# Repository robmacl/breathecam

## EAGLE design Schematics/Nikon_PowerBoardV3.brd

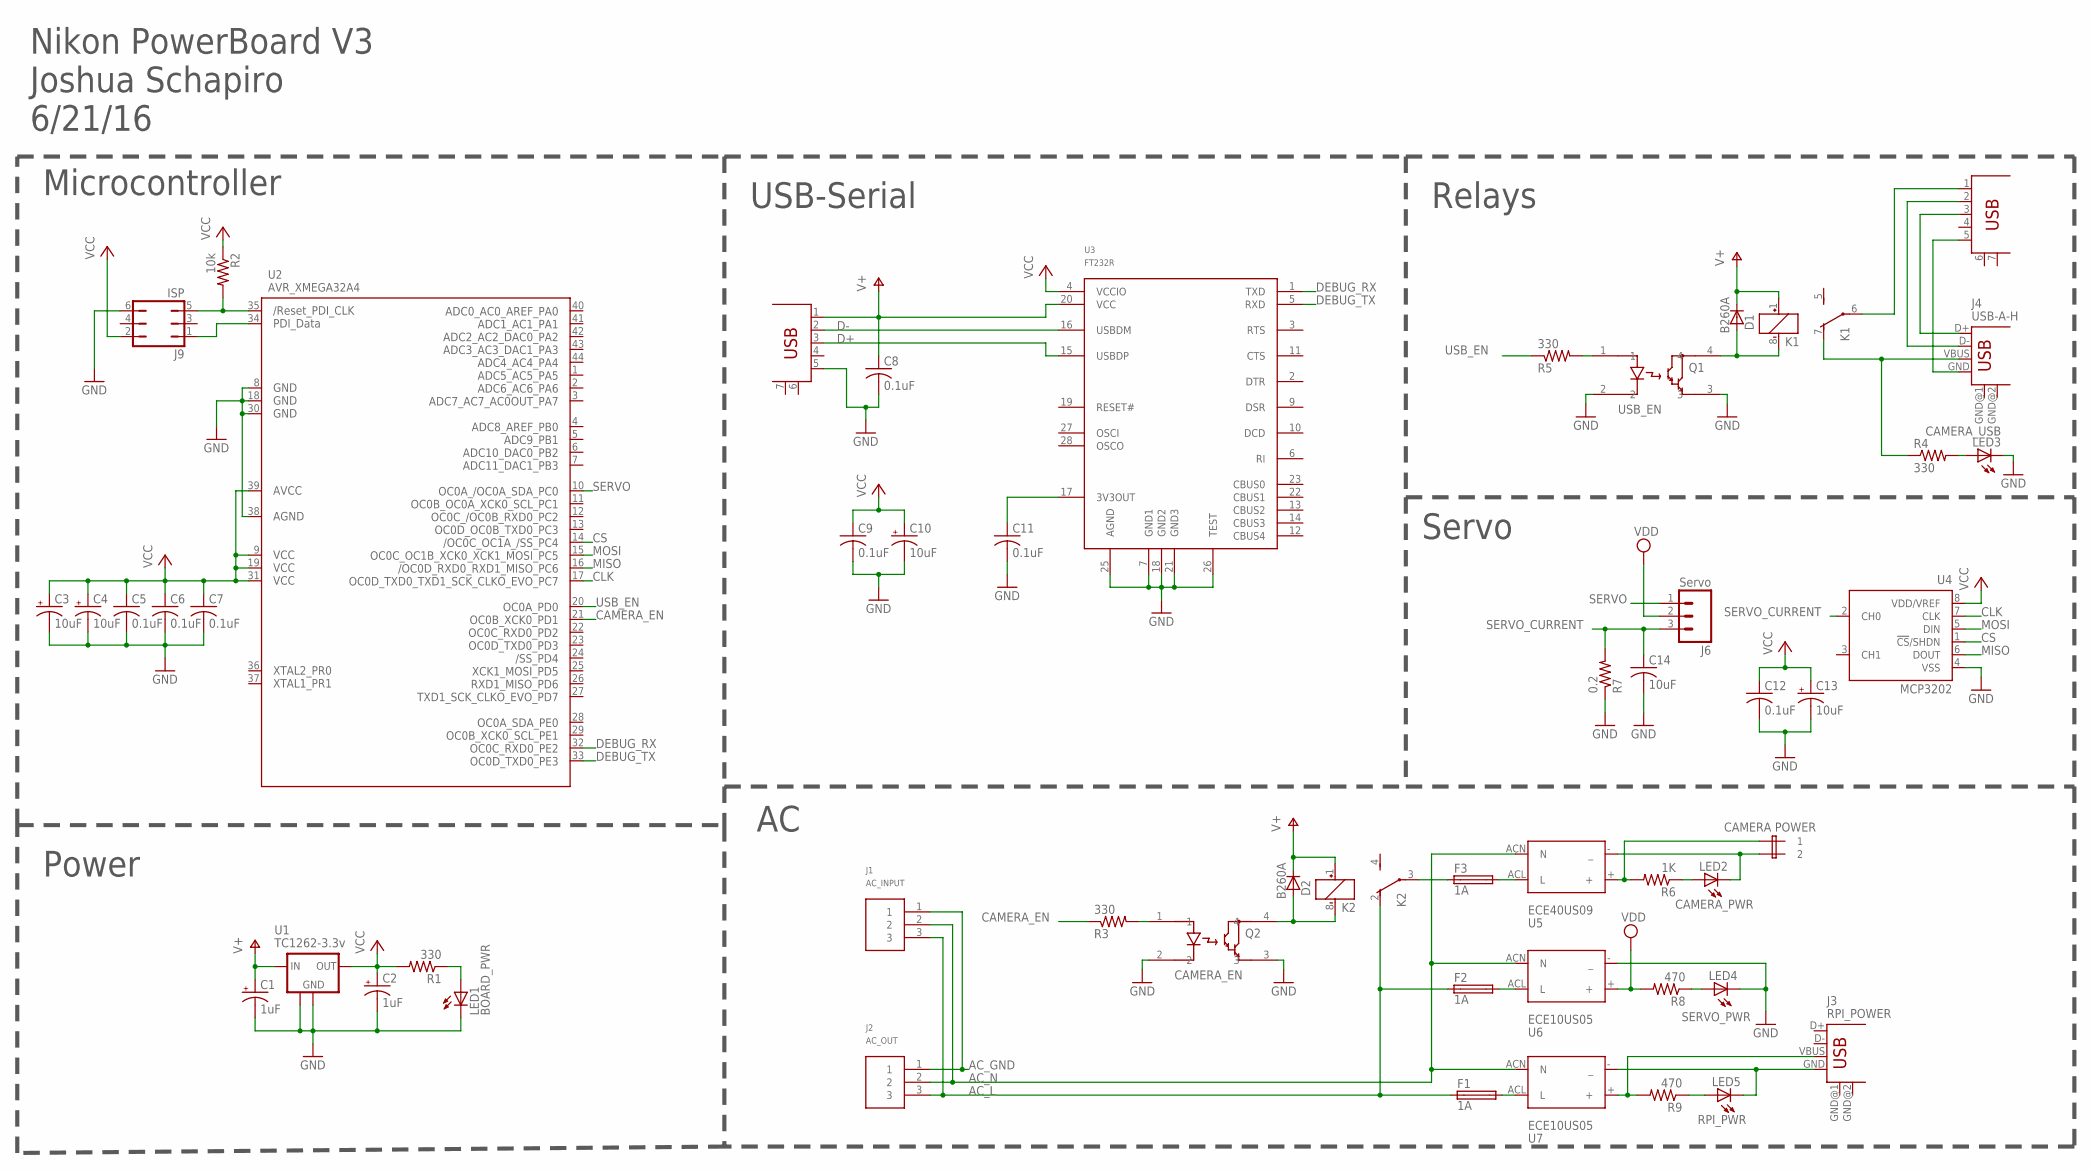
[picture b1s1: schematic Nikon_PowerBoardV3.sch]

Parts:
C1, C2: 1uF; EIA3216
C3, C4, C10, C13: 10uF; EIA3216
C5, C6, C7, C8, C9, C11, C12: 0.1uF; C0603
C14: 10uF; C1206
D1, D2: B260A; SMA-DIODE
F1, F2, F3: 1A; 19560
J1: AC_INPUT; 3-PIN-SCREW
J2: AC_OUT; 3-PIN-SCREW
J3: RPI_POWER; USB-A-H
J4: USB-A-H
J5: CAMERA POWER; 2-PIN_SCREWTERM
J6: Servo; 1X03_LONGPADS
J7, J8: MICRO-USB; MICRO_USB_SM_W/_TO_PINS
J9: ISP; JP3Q
K1: USB_EN; G6K-2F
K2: CAMERA_EN; G6K-2F
LED1: BOARD_PWR; CHIPLED_0603
LED2: CAMERA_PWR; CHIPLED_0603
LED3: CAMERA_USB; CHIPLED_0603
LED4: SERVO_PWR; CHIPLED_0603
LED5: RPI_PWR; CHIPLED_0603
Q1: USB_EN; 4-PIN_MINI-FLAT
Q2: CAMERA_EN; 4-PIN_MINI-FLAT
R1, R3, R4, R5: 330; R0603
R2: 10k; R0603
R6: 1K; R0603
R7: 0.2; R1206
R8, R9: 470; R0603
U1: TC1262-3.3v; SOT223
U2: AVR_XMEGA32A4; TQFP44
U3: FT232R; SSOP28
U4: MCP3202; SO-08
U5: ECE40US09; EC40
U6, U7: ECE10US05; ECE10

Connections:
AC_GND: J1.1, J2.1
AC_L: F1.1, F2.1, J1.3, J2.3, K2.2 (O)
AC_N: J1.2, J2.2, U5.ACN (N), U6.ACN (N), U7.ACN (N)
CAMERA_EN: R3.1, U2.21 (PD1)
CLK: U2.17 (PC7), U4.7 (CLK)
CS: U2.14 (PC4), U4.1 (!CS!/SHDN)
D+: J8.3 (D+), U3.15 (USBDP)
D-: J8.2 (D-), U3.16 (USBDM)
DEBUG_RX: U2.32 (PE2), U3.1 (TXD)
DEBUG_TX: U2.33 (PE3), U3.5 (RXD)
GND: C1.C (-), C2.C (-), C3.C (-), C4.C (-), C5.2, C6.2, C7.2, C8.2, C9.2, C10.C (-), C11.2, C12.2, C13.C (-), C14.2, J8.5 (GND), J9.6, LED1.C, LED3.C, LED4.C, Q1.2, Q1.3, Q2.2, Q2.3, R7.1, U1.2 (GND), U1.4 (GND1), U2.8 (GND1), U2.18 (GND2), U2.30 (GND3), U2.38 (AGND), U3.7 (GND1), U3.18 (GND2), U3.21 (GND3), U3.25 (AGND), U3.26 (TEST), U4.4 (VSS), U6.- (_)
MISO: U2.16 (PC6), U4.6 (DOUT)
MOSI: U2.15 (PC5), U4.5 (DIN)
unnamed: J9.1, U2.34 (PDI_DATA)
unnamed: J4.GND, J7.5 (GND)
unnamed: F3.1, K2.3
unnamed: LED1.A, R1.1
unnamed: Q1.1, R5.2
unnamed: J9.5, R2.2, U2.35 (RESET)
unnamed: D2.A, K2.8 (-), Q2.4
unnamed: J7.1 (VBUS), K1.6
unnamed: LED3.A, R4.2
unnamed: Q2.1, R3.2
unnamed: J3.VBUS, R9.2, U7.+
unnamed: F3.2, U5.ACL (L)
unnamed: F2.2, U6.ACL (L)
unnamed: F1.2, U7.ACL (L)
unnamed: LED4.A, R8.1
unnamed: J5.P$1 (1), R6.2, U5.+
unnamed: C11.1, U3.17 (3V3OUT)
unnamed: LED2.A, R6.1
unnamed: J5.P$2 (2), LED2.C, U5.- (_)
unnamed: J3.GND, LED5.C, U7.- (_)
unnamed: LED5.A, R9.1
unnamed: J4.VBUS, K1.7 (O), R4.1
unnamed: J4.D+, J7.3 (D+)
unnamed: J4.D-, J7.2 (D-)
unnamed: D1.A, K1.8 (-), Q1.4
SERVO: J6.1, U2.10 (PC0)
SERVO_CURRENT: C14.1, J6.3, R7.2, U4.2 (CH0)
USB_EN: R5.1, U2.20 (PD0)
V+: C1.A (+), C8.1, D1.C, D2.C, J8.1 (VBUS), K1.1 (+), K2.1 (+), U1.1 (IN), U3.20 (VCC)
VCC: C2.A (+), C3.A (+), C4.A (+), C5.1, C6.1, C7.1, C9.1, C10.A (+), C12.1, C13.A (+), J9.2, R1.2, R2.1, U1.3 (OUT), U2.9 (VCC1), U2.19 (VCC2), U2.31 (VCC3), U2.39 (AVCC), U3.4 (VCCIO), U4.8 (VDD/VREF)
VDD: J6.2, R8.2, U6.+

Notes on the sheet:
Nikon PowerBoard V3 Joshua Schapiro 6/21/16
Microcontroller
USB-Serial
Relays
Power
Servo
CAMERA POWER

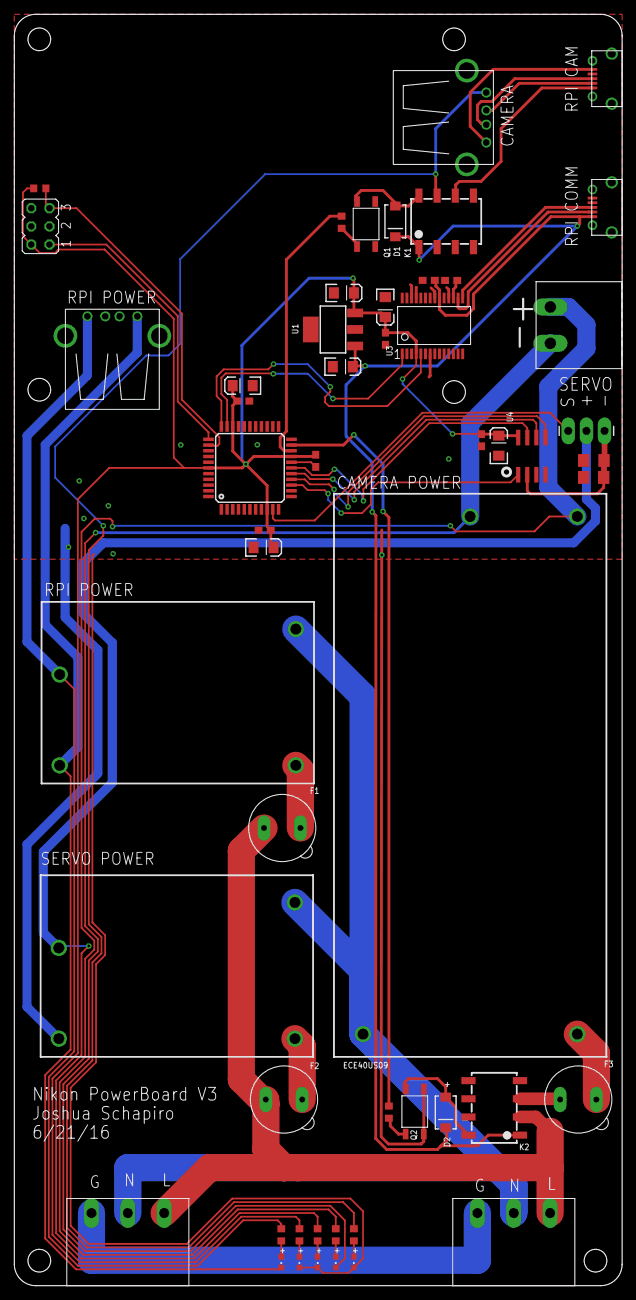
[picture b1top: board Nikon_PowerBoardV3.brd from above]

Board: 2 copper layers, 85.0 x 177.8 mm, 53 parts (0 on the bottom side), 44 nets.

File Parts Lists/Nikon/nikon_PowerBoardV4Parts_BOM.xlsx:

Quantity | Reference | Part | Part Number | Distributor | Manufacturer part number
1 | U2 | Microcontroller | ATXMEGA32A4-AU-ND | Digikey | ATXMEGA32A4-AU
1 | U1 | TC1262-3.0v | TC1262-3.0VDB-ND | Digikey | TC1262-3.0VDB
1 | U3 | FT232R | 768-1007-1-ND | Digikey | FT232RL-REEL
1 | U4 | MCP3202 | MCP3202-CI/SN-ND | Digikey | MCP3202-CI/SN
2 | U6, U7 | 5v supply | 1470-1115-ND | Digikey | ECE10US05
1 | U5 | 9v supply | 1470-1134-ND | Digikey | ECE40US09
2 | Q1, Q2 | 425-2098-1-ND | optocoupler | Digikey | PC365NJ0000F
2 | K1, K2 | Z112CT-ND | relay | Digikey | G6K-2F-TR DC5
5 | LED1, LED2, LED3, LED4, LED5 | 160-1435-1-ND | green leds 0603 | Digikey | LTST-C190KGKT
2 | D1, D2 | B260A-FDICT-ND | diode for relay | Digikey | B260A-13-F
3 | F1, F2, F3 | WK0001-ND | fuse holder | Digikey | 56000001319
2 | J1, J2 | APC1259-ND | 3-pin screw terminal | Digikey | ELFH03210
1 | J5 | 609-3907-ND | screw terminal header | Digikey | 20020110-H021A01LF
2 | J7, J8 | 609-4618-1-ND | usb - micro | Digikey | 10118194-0001LF
2 | J3, J4 | 1175-1015-ND | usb - A | Digikey | 1002-001-01000
1 | J9 | 952-2121-ND | isp header | Digikey | M20-9980346
1 | J6 | 609-3461-ND | 3-pin header | Digikey | 68000-103HLF
4 | R1, R3, R4, R5 | 311-330HRCT-ND | 330R 0603 resistor | Digikey | RC0603FR-07330RL
2 | R8, R9 | 311-470GRCT-ND | 470R 0603 resistor | Digikey | RC0603JR-07470RL
1 | R6 | 311-1.0KGRCT-ND | 1k 0603 resistor | Digikey | RC0603JR-071KL
1 | R2 | P10KGCT-ND | 10k 0603 resistor | Digikey | ERJ-3GEYJ103V
1 | R7 | CRL1206-FW-R200ELFCT-ND | 0.2R 1206 resistor | Digikey | CRL1206-FW-R200ELF
1 | R10 | A121216CT-ND | 300R 2512 resistor | Digikey | 3522300RFT
7 | C5, C6, C7, C8, C9, C11, C12 | 490-1575-1-ND | 0.1uF 0603 ceramic capacitor | Digikey | GRM188F51E104ZA01D
2 | C1, C2 | 399-3678-1-ND | 1uf 1206 tantalum capacitor | Digikey | T491A105K016AT
4 | C3, C4, C10, C13 | 495-2174-1-ND | 10uf 1206 tantalum capacitor | Digikey | T491A106M004AT
1 | C14 | 1276-1312-1-ND | 10uF 1206 cermic capacitor | Digikey | CL31F106ZOHNNNE

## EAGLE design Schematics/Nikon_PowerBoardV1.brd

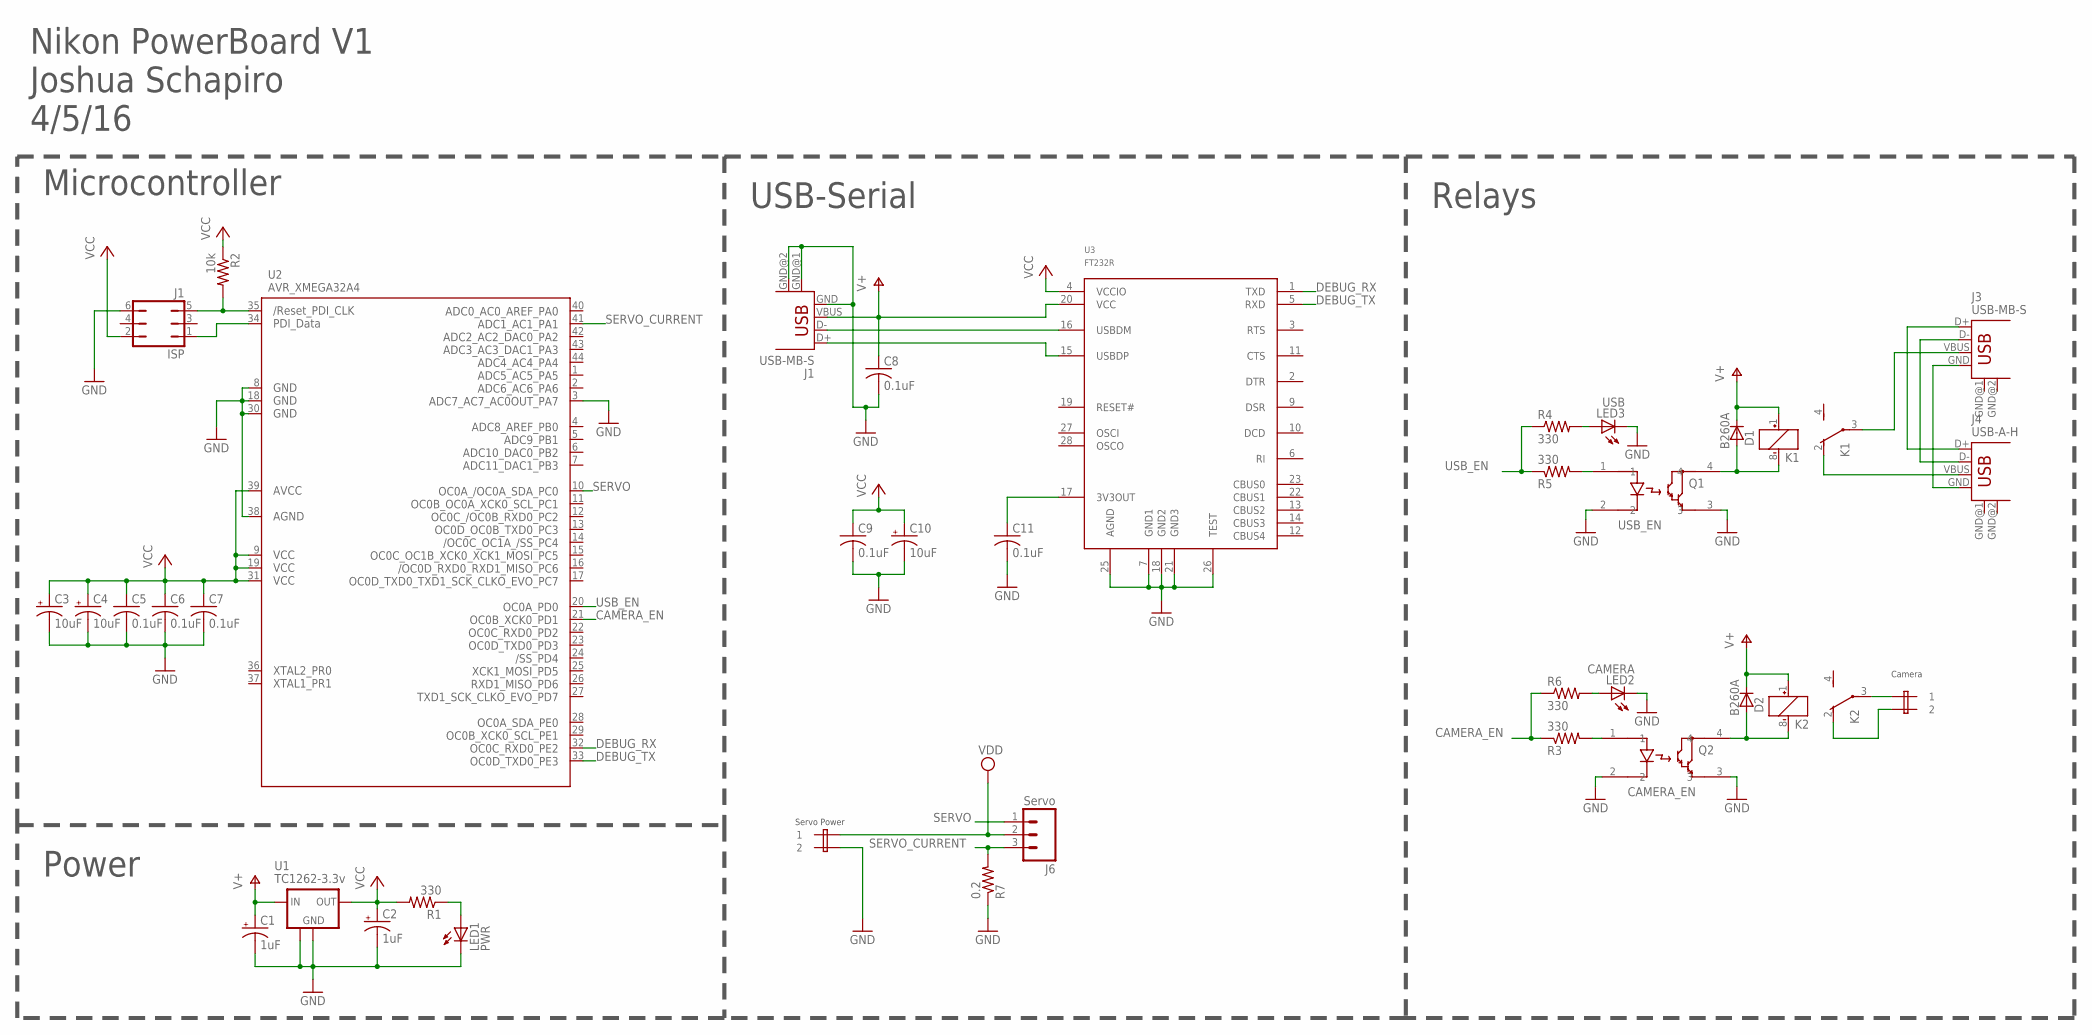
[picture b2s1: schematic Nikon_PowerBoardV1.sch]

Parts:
C1, C2: 1uF; EIA3216
C3, C4, C10: 10uF; EIA3216
C5, C6, C7, C8, C9, C11: 0.1uF; C1206
D1, D2: B260A; SMA-DIODE
ISP: J1; JP3Q
J1, J3: USB-MB-S
J2: Camera; 2-PIN_SCREWTERM
J4: USB-A-H
J5: ServoPower; 2-PIN_SCREWTERM
J6: Servo; 1X03_LONGPADS
K1: USB_EN; G6K-2F
K2: CAMERA_EN; G6K-2F
LED1: PWR; CHIPLED_1206
LED2: CAMERA; CHIPLED_1206
LED3: USB; CHIPLED_1206
Q1: USB_EN; 4-PIN_MINI-FLAT
Q2: CAMERA_EN; 4-PIN_MINI-FLAT
R1, R3, R4, R5, R6: 330; R1206
R2: 10k; R1206
R7: 0.2; R1206
U1: TC1262-3.3v; SOT223
U2: AVR_XMEGA32A4; TQFP44
U3: FT232R; SSOP28

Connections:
CAMERA_EN: R3.1, R6.1, U2.21 (PD1)
DEBUG_RX: U2.32 (PE2), U3.1 (TXD)
DEBUG_TX: U2.33 (PE3), U3.5 (RXD)
GND: C1.C (-), C2.C (-), C3.C (-), C4.C (-), C5.2, C6.2, C7.2, C8.2, C9.2, C10.C (-), C11.2, ISP.6, J1.GND, J1.GND@1 (GND), J1.GND@2 (GND), J5.P$2 (2), LED1.C, LED2.C, LED3.C, Q1.2, Q1.3, Q2.2, Q2.3, R7.1, U1.2 (GND), U1.4 (GND1), U2.3 (PA7), U2.8 (GND1), U2.18 (GND2), U2.30 (GND3), U2.38 (AGND), U3.7 (GND1), U3.18 (GND2), U3.21 (GND3), U3.25 (AGND), U3.26 (TEST)
J2: J3.D+, J4.D+
unnamed: ISP.1, U2.34 (PDI_DATA)
unnamed: J3.GND, J4.GND
unnamed: J3.D-, J4.D-
unnamed: LED1.A, R1.1
unnamed: Q1.1, R5.2
unnamed: ISP.5, R2.2, U2.35 (RESET)
unnamed: D2.A, K2.8 (-), Q2.4
unnamed: J3.VBUS, K1.3
unnamed: J4.VBUS, K1.2 (O)
unnamed: LED3.A, R4.2
unnamed: Q2.1, R3.2
unnamed: J1.D-, U3.16 (USBDM)
unnamed: J1.D+, U3.15 (USBDP)
unnamed: J2.P$1 (1), K2.3
unnamed: J2.P$2 (2), K2.2 (O)
unnamed: C11.1, U3.17 (3V3OUT)
unnamed: LED2.A, R6.2
unnamed: D1.A, K1.8 (-), Q1.4
SERVO: J6.1, U2.10 (PC0)
SERVO_CURRENT: J6.3, R7.2, U2.41 (PA1)
USB_EN: R4.1, R5.1, U2.20 (PD0)
V+: C1.A (+), C8.1, D1.C, D2.C, J1.VBUS, K1.1 (+), K2.1 (+), U1.1 (IN), U3.20 (VCC)
VCC: C2.A (+), C3.A (+), C4.A (+), C5.1, C6.1, C7.1, C9.1, C10.A (+), ISP.2, R1.2, R2.1, U1.3 (OUT), U2.9 (VCC1), U2.19 (VCC2), U2.31 (VCC3), U2.39 (AVCC), U3.4 (VCCIO)
VDD: J5.P$1 (1), J6.2

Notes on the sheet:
Camera
Nikon PowerBoard V1 Joshua Schapiro 4/5/16
Microcontroller
USB-Serial
Relays
Power
Servo Power

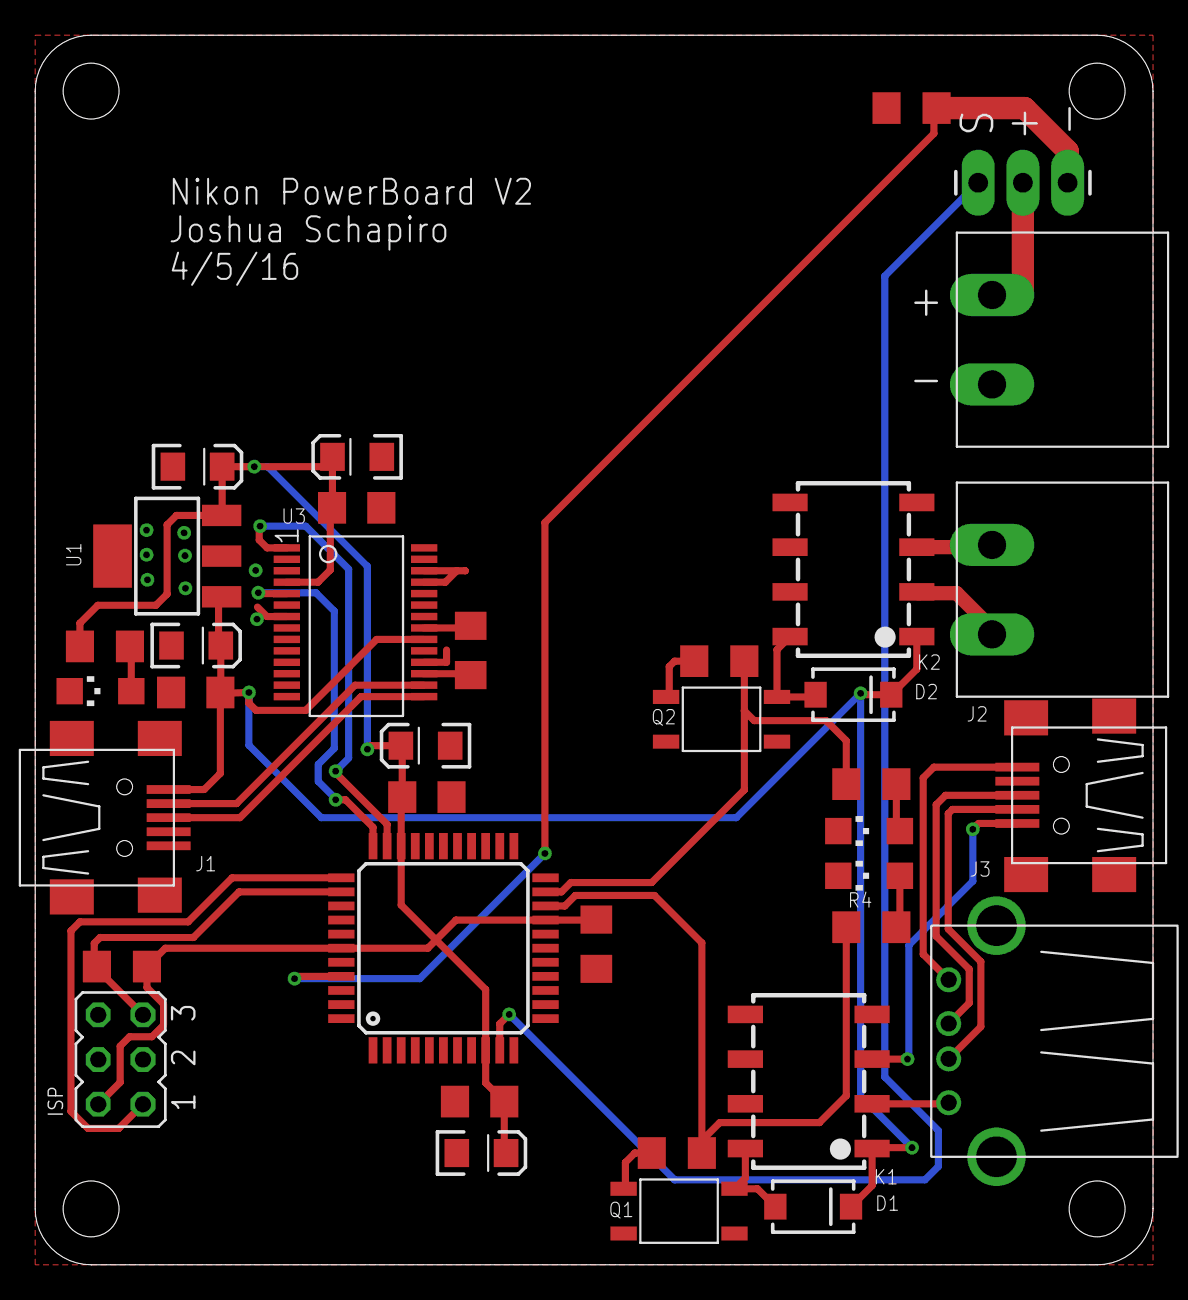
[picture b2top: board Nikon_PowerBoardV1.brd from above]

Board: 2 copper layers, 63.5 x 69.8 mm, 37 parts (0 on the bottom side), 29 nets.

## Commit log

2022-03-16 Code and design files for BreatheCam cameras.
2022-03-23 Deleted old image of the 'requests' package in nikon/install/requests, added new CAD files in CAD/pi_cam
2022-04-05 Modified camera_mount.SLDPRT to allow access to focus lock screw using hex key. Fixed the mounting slots in mount_plate.SLDPRT some more.
2022-04-06 Various changes to improve fit of the mount within the housing. Also added stiffeners to the plate and incorporated the standoffs into the plate.
2022-04-09 Made some test parts for tweaking mounting hole sizes, and moved the mount slots so we are 5mm farther back.
2022-04-14 More tweaks to CAD/pi_cam related to integral standoff holes and front relief for cameras (mainly to improve front side access to lens).
2022-04-15 Added Code/pi_cam, very much work in progress
2022-04-19 imageService.py is approaching something testable
2022-04-20 imageService.py now runs
2022-04-20 uploadToServer is now working
2022-04-26 Resurrected ping processes, changed to .ini style config file. Log entries now have the service name. Tweaked logging usage so that a useful amount of info is present at the INFO level.
    takeImage_launcher.sh ==> imageService_launcher.sh
    run_all.sh (new)
    Launch all the launchers
    kill_all.sh: (new)
    Kill all the processes by name using pkill
    config_files/breathecam.ini (new)
2022-05-03 Change udpPinger to use logger, but also dont launch it from run_all.sh
2022-05-04 imageService.py: create "images" directory
    *_launcher.sh
    pingServer.py:
    Launcher scripts now save any output in logs/
    Watchdog function is moved from imageService_launcher.sh to pingServer_launcher.sh
    serviceConfig.py:
    Now there is only one log file, breathecam.txt, and this does not have the
2022-05-04 Minor changes to startup scripts and error code
2022-05-18 Fixes to startup scripts and watchdog feature. Now startup at reboot is working.
    Code/pi_cam/imageService.py:
    Documentation for grab_cmd, add --rotation 180 for test camera
    Code/pi_cam/pingServer.py:
    -- Make named parameters for watchdog parameters
    -- Reckon image age from the oldest image since last ping failure. This
    avoids a spurious watchdog message on startup.
2022-05-18 More tweaks to watchdog and reboot function. Now actually working reliably?
    Code/pi_cam/pingServer.py:
    Revert change to not count old image files for age, and if no files, treat as
    very old. We want to fail if at start capture is already failing, and if
    there are no files at all. Reduced watchdog_threshold from 10 to 5 and
    age_threshold from 120 to 60. I don't think there is much point in delaying
    reboot more than that.
2022-05-19 More emphatic reboot action in pingServer_launcher.sh
2022-05-19 Added more to notes.txt about system install, remote access, VNC, etc.
2022-05-20 moved camera parameters to config file
2022-05-30 Notes update
2022-06-02 Notes
2022-06-07 Multi-camera support with Arducam multiplexer.
    Code/pi_cam/config_files/breathecam.ini:
    Update for "piquad" multi-camera setup.
    Code/pi_cam/imageService.py:
    Code/pi_cam/serviceConfig.py:
    Camera mux support. Got rid of some camera parameter caching in serviceConfig
    Code/pi_cam/pingServer.py:
2022-06-23 Start mechanical work on 4 rPi camera
2022-06-27 For quad pi mechanical design, revised holder setup for card cage, added cooling air components.
2022-06-28 Changes to get non-mux mode working again like it should, updates to notes.txt
2022-07-11 A lot of fiddling with the snap clip design on air_top.SLDPRT and refactoring of the relations between the air_XXX and the other bits of the assembly.
2022-07-13 Tweaks to air_box, air_top increasing thickness back to 1.6mm, since the 1.2mm was printing unreliably and pretty flimsy. Added fillets. On camera_mount_assy_4pi, removed the clamp bosses, moved the 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
2022-07-15 Updatess to CAD/pi_cam. Added stiffeners to mount_plate_4pi.SLDPRT and chamfer the mount keyholes. Add compliant blower mount to air_top.SLDPRT for vibration reduction. Thin air_box.SLDPRT to make th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
2022-07-18 Tweaks to mount_plate_4pi.SLDPRT to increase stiffness and improve the alignment of the slots with the enclosure.
2022-07-26 New power_mount.SLDPRT for holding Ethernet switch and power supply. Tweaks to camera_mount.SLDPRT intended to reduce warping, less material in the mount flange, stiffener ribs on the front.
